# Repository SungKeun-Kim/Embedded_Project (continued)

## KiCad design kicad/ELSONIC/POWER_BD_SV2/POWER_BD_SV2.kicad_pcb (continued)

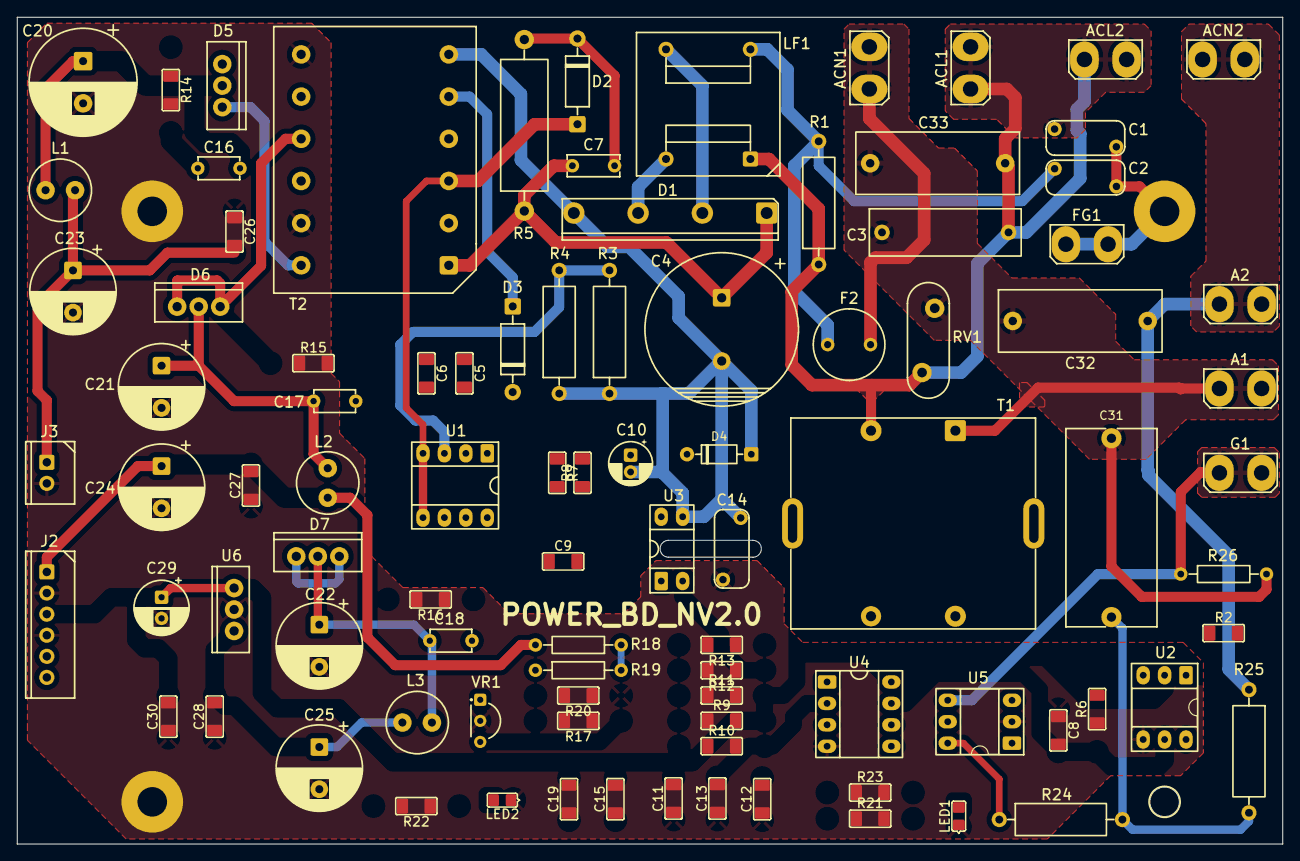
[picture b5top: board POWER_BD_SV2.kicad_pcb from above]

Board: 2 copper layers, 150.0 x 98.0 mm, 97 parts (0 on the bottom side), 51 nets.
